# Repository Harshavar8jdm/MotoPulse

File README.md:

# MotoPulse

A robust, solid-state motorcycle turn signal controller powered by an STM32G0 microcontroller and high-current TO-220 MOSFETs. Built to replace unreliable mechanical flashers, this board handles heavy vehicle vibrations and features high-power thermal handling and noise isolation for automotive environments.

---

## Visuals

| 3D Render (Top) | 3D Render (Bottom) | PCB Layout |
|---|---|---|
|  |  |  |

### Schematic Diagram

---

## Features

* **Solid-State Reliability:** Swaps out clunky mechanical relays for rugged TO-220 MOSFET switching.
* **High Current Support:** Safely handles up to 3A per channel—compatible with both OEM halogen bulbs and aftermarket LEDs.
* **Automotive Protection:** Includes onboard fuse safety, reverse polarity protection diodes, and input voltage clamping.
* **Noise Isolated Design:** Employs a solid bottom-layer ground plane to block high-frequency motorcycle ignition and alternator interference.

---

## Hardware Specifications

* **Microcontroller:** STM32G030F6P6
* **Power Input:** 12V DC (Vehicle Battery)
* **Logic Voltage:** 3.3V Regulated (via dedicated onboard LDO)
* **Outputs:** 4x Independent MOSFET switched high-side channels
* **PCB Specs:** 2 Layers, 1 oz Copper, JLCPCB compatible constraints

---

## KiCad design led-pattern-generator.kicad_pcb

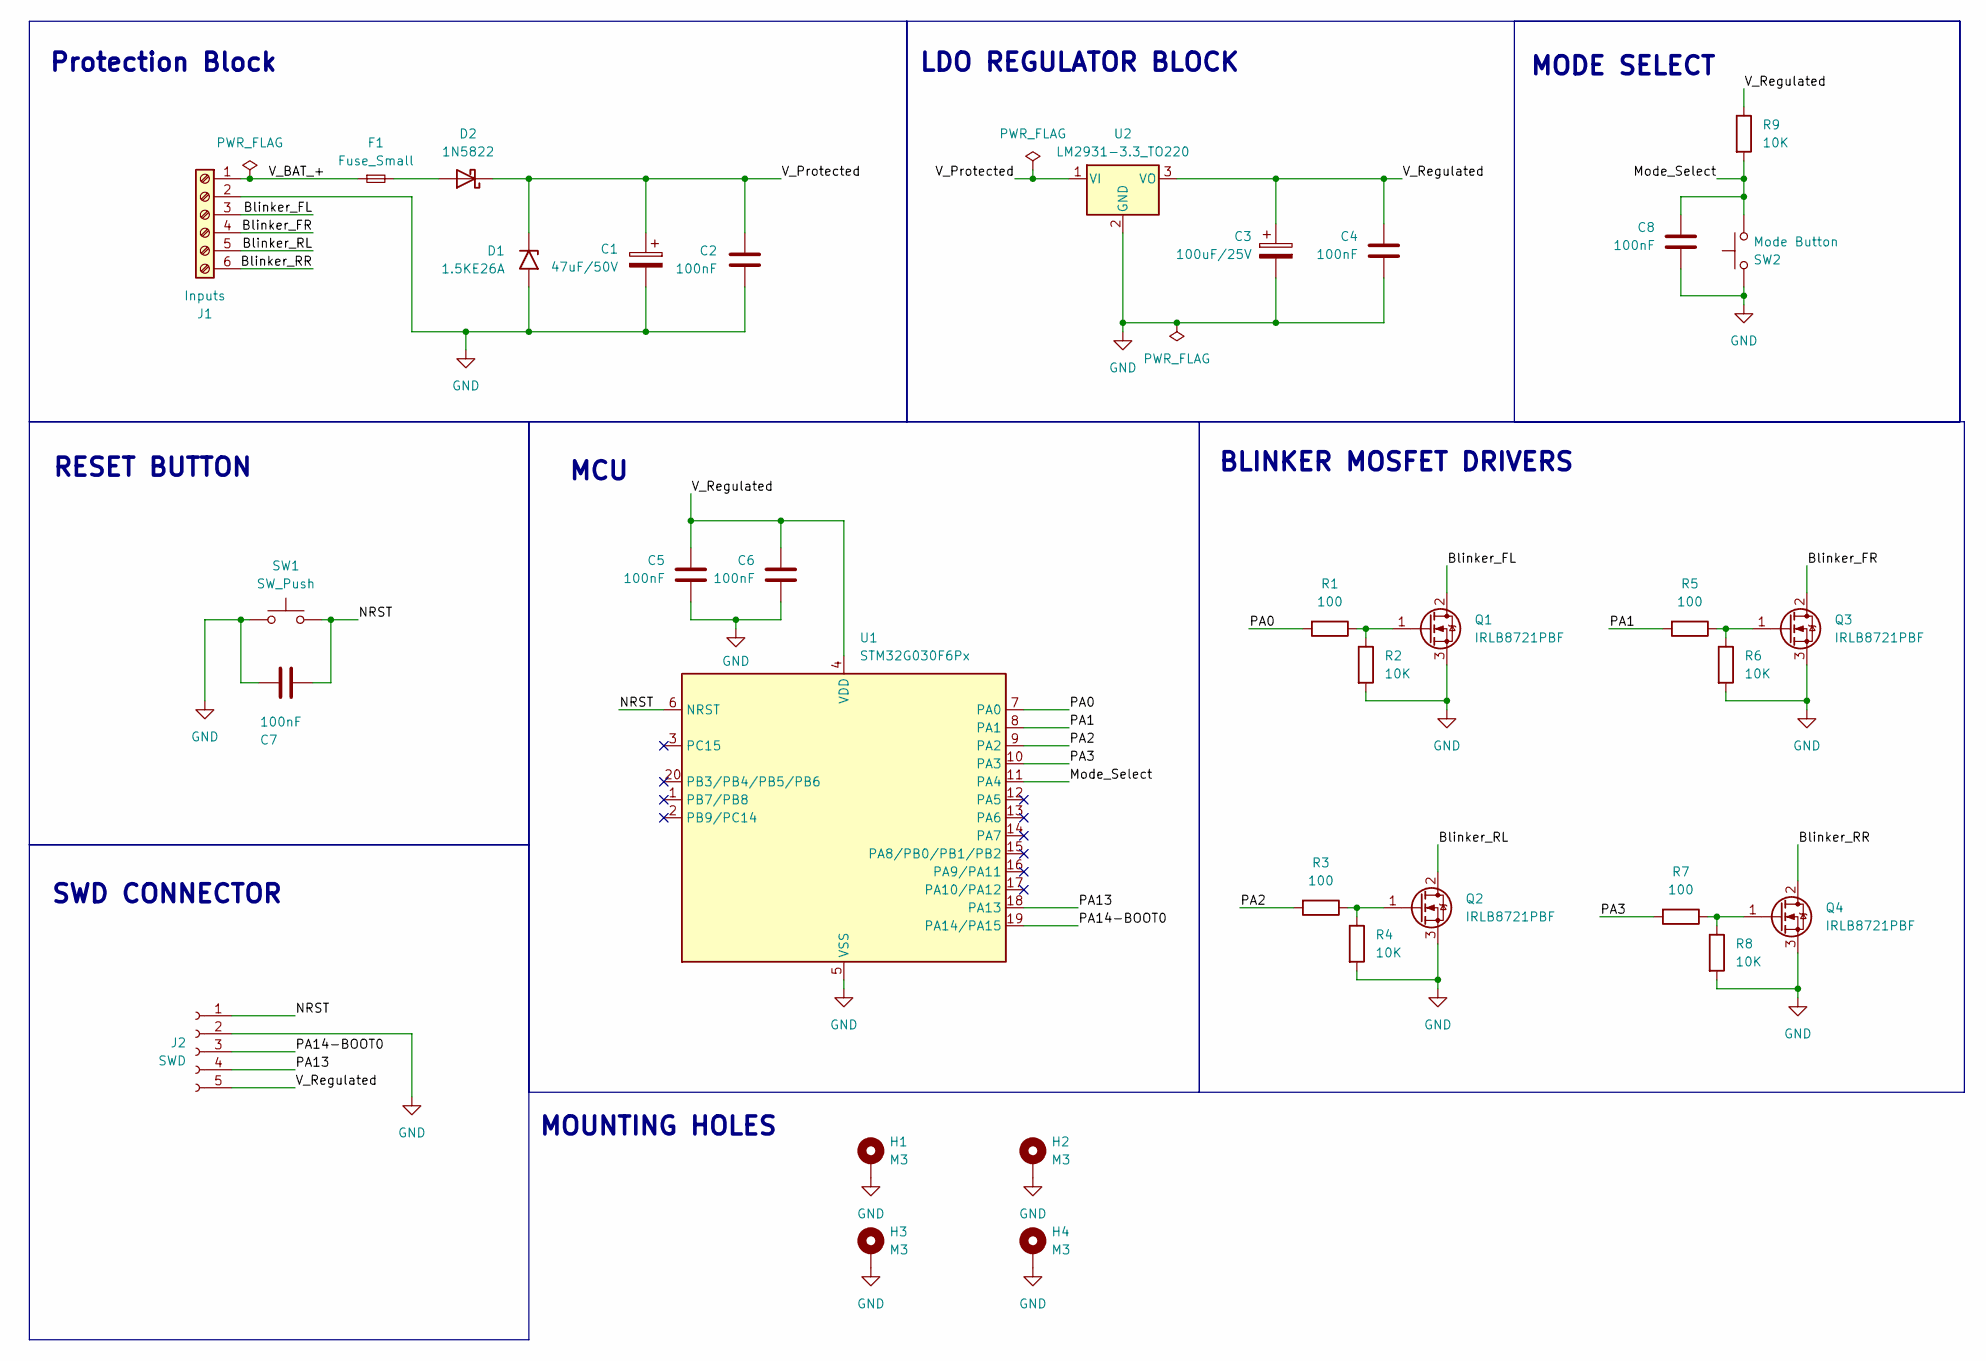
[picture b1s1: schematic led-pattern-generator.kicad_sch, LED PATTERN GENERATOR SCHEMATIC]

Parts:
C1: 47uF/50V; CP_Radial_D6.3mm_P2.50mm
C2, C4, C5, C6, C7, C8: 100nF; C_Disc_D5.0mm_W2.5mm_P2.50mm
C3: 100uF/25V; CP_Radial_D6.3mm_P2.50mm
D1: 1.5KE26A; D_DO-201AE_P15.24mm_Horizontal
D2: 1N5822; D_DO-201AD_P15.24mm_Horizontal
F1: Fuse_Small; Fuseholder_Littelfuse_100_series_5x20mm
H1, H2, H3, H4: M3; MountingHole_3.2mm_M3_DIN965_Pad
J1: Inputs; TerminalBlock_Phoenix_MKDS-3-6-5.08_1x06_P5.08mm_Horizontal
J2: SWD; PinSocket_1x05_P2.54mm_Horizontal
Q1, Q2, Q3, Q4: IRLB8721PBF; TO-220-3_Vertical
R1, R3, R5, R7: 100; R_Axial_DIN0207_L6.3mm_D2.5mm_P7.62mm_Horizontal
R2, R4, R6, R8, R9: 10K; R_Axial_DIN0207_L6.3mm_D2.5mm_P7.62mm_Horizontal
SW1: SW_Push; SW_PUSH_6mm
SW2: Mode Button; SW_PUSH_6mm
U1: STM32G030F6Px; TSSOP-20_4.4x6.5mm_P0.65mm
U2: LM2931-3.3_TO220; TO-220-3_Vertical

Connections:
/Blinker_FL: J1.3, Q1.2 (D)
/Blinker_FR: J1.4, Q3.2 (D)
/Blinker_RL: J1.5, Q2.2 (D)
/Blinker_RR: J1.6, Q4.2 (D)
/Mode_Select: C8.1, R9.2, SW2.1, U1.11 (PA4)
/NRST: C7.2, J2.1, SW1.2, U1.6 (NRST)
/PA0: R1.2, U1.7 (PA0)
/PA1: R5.2, U1.8 (PA1)
/PA2: R3.2, U1.9 (PA2)
/PA3: R7.2, U1.10 (PA3)
/PA13: J2.4, U1.18 (PA13)
/PA14-BOOT0: J2.3, U1.19 (PA14/PA15)
/V_BAT_+: F1.1, J1.1
/V_Protected: C1.1, C2.1, D1.1 (A1), D2.1 (K), U2.1 (VI)
/V_Regulated: C3.1, C4.1, C5.1, C6.1, J2.5, R9.1, U1.4 (VDD), U2.3 (VO)
GND: C1.2, C2.2, C3.2, C4.2, C5.2, C6.2, C7.1, C8.2, D1.2 (A2), H1.1 (1_1), H2.1 (1_1), H3.1 (1_1), H4.1 (1_1), J1.2, J2.2, Q1.3 (S), Q2.3 (S), Q3.3 (S), Q4.3 (S), R2.2, R4.2, R6.2, R8.2, SW1.1, SW2.2, U1.5 (VSS), U2.2 (GND)
unnamed: D2.2 (A), F1.2
unnamed: Q1.1 (G), R1.1, R2.1
unnamed: Q2.1 (G), R3.1, R4.1
unnamed: Q3.1 (G), R5.1, R6.1
unnamed: Q4.1 (G), R7.1, R8.1

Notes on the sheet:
MCU
MODE SELECT
MOUNTING HOLES
BLINKER MOSFET DRIVERS
Protection Block
LDO REGULATOR BLOCK
RESET BUTTON
SWD CONNECTOR

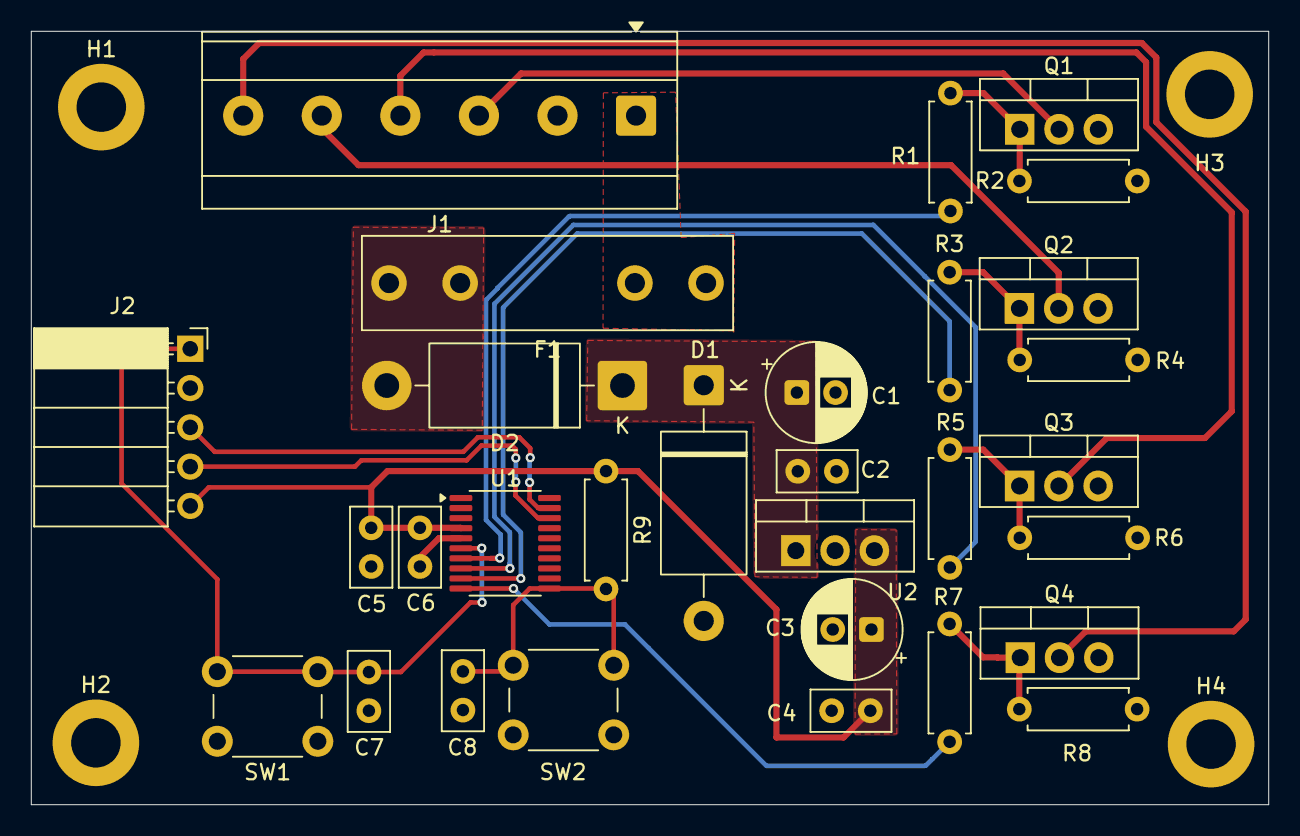
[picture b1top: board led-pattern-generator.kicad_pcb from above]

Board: 2 copper layers, 80.0 x 50.0 mm, 34 parts (0 on the bottom side), 21 nets.
